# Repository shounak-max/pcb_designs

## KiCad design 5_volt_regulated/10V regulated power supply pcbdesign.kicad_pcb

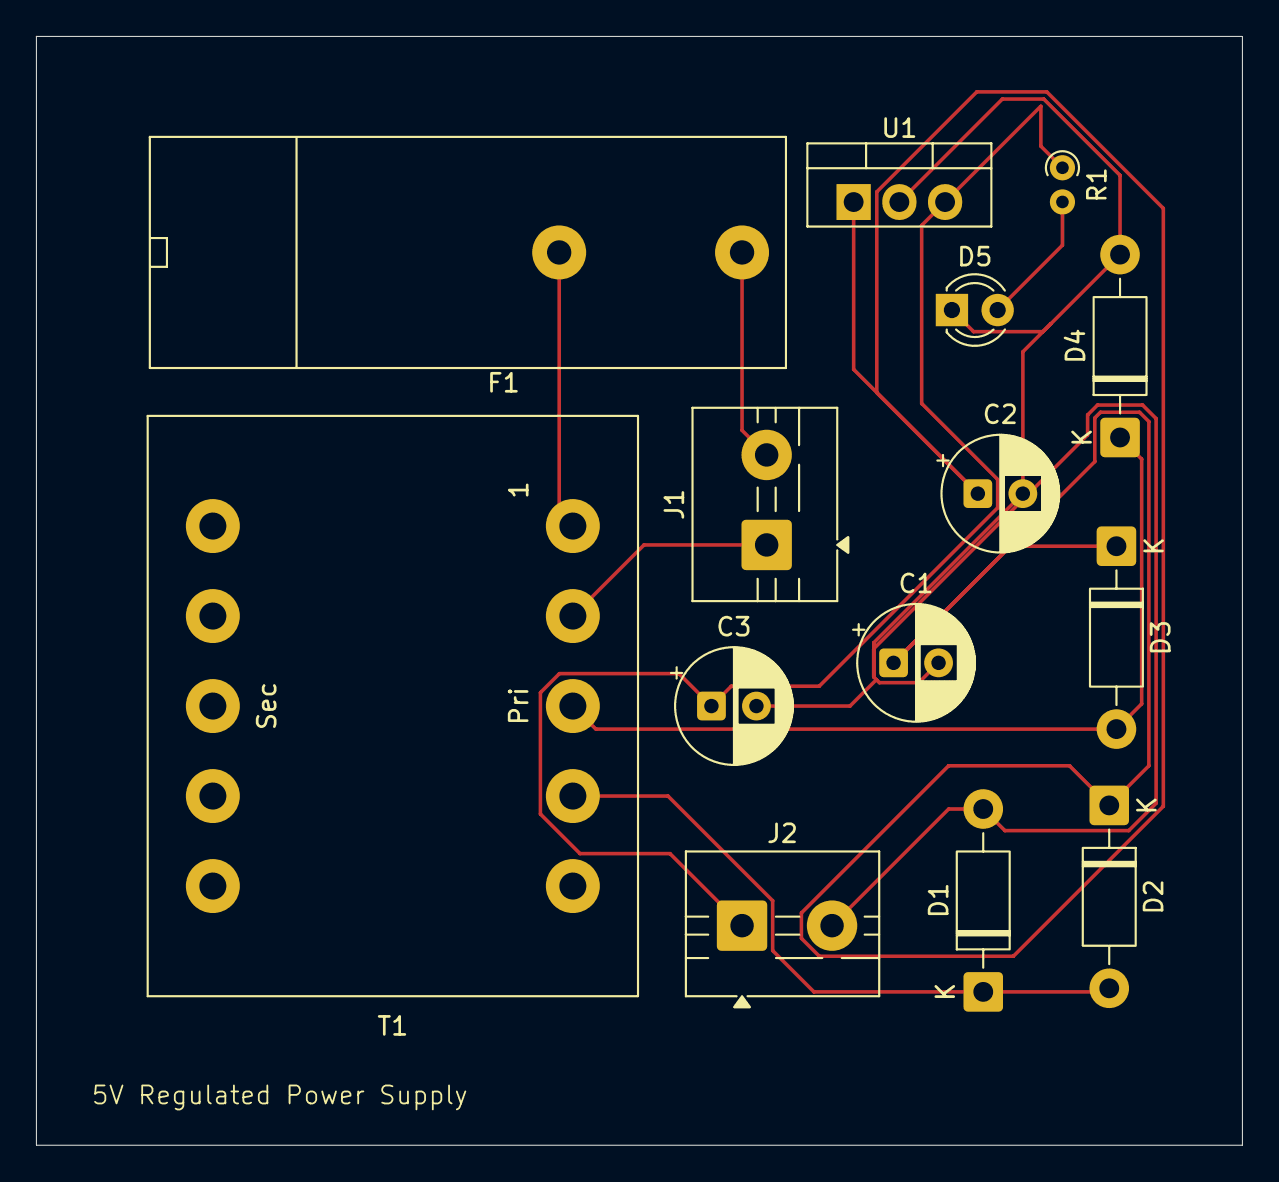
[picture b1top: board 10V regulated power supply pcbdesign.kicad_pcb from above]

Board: 2 copper layers, 67.0 x 61.6 mm, 14 parts (0 on the bottom side), 9 nets.

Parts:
C1: 470uF; CP_Radial_D6.3mm_P2.50mm
C2, C3: 0.1uF; CP_Radial_D6.3mm_P2.50mm
D1, D2, D3, D4: 1N4007; D_DO-41_SOD81_P10.16mm_Horizontal
D5: LED; LED_D3.0mm
F1: Fuse; Fuseholder_Cylinder-5x20mm_Bulgin_FX0457_Horizontal_Closed
J1: AC_INPUT; TerminalBlock_MaiXu_MX126-5.0-02P_1x02_P5.00mm
J2: (+5v, gnd); TerminalBlock_MaiXu_MX126-5.0-02P_1x02_P5.00mm
R1: 150; R_Axial_DIN0204_L3.6mm_D1.6mm_P1.90mm_Vertical
T1: Transformer_1P_1S; Transformer_CHK_EI30-2VA_1xSec
U1: L7805; TO-220-3_Vertical

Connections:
GND: C1.2, C2.2, C3.2, D1.2 (A), D4.2 (A), D5.1 (K), J2.2, U1.2 (GND)
unnamed: D1.1 (K), D2.2 (A), T1.4 (SB)
unnamed: C1.1, C2.1, D2.1 (K), D3.1 (K), U1.1 (IN)
unnamed: D3.2 (A), D4.1 (K), T1.3 (SA)
unnamed: D5.2 (A), R1.2
unnamed: J1.1, T1.2 (AB)
unnamed: F1.1, J1.2
unnamed: C3.1, J2.1, R1.1, U1.3 (OUT)
unnamed: F1.2, T1.1 (AA)

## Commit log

2026-02-06 badmosh_paul_commit
2026-02-07 nessesary commits inc changing the file name to harass paul
2026-02-07 fixes
